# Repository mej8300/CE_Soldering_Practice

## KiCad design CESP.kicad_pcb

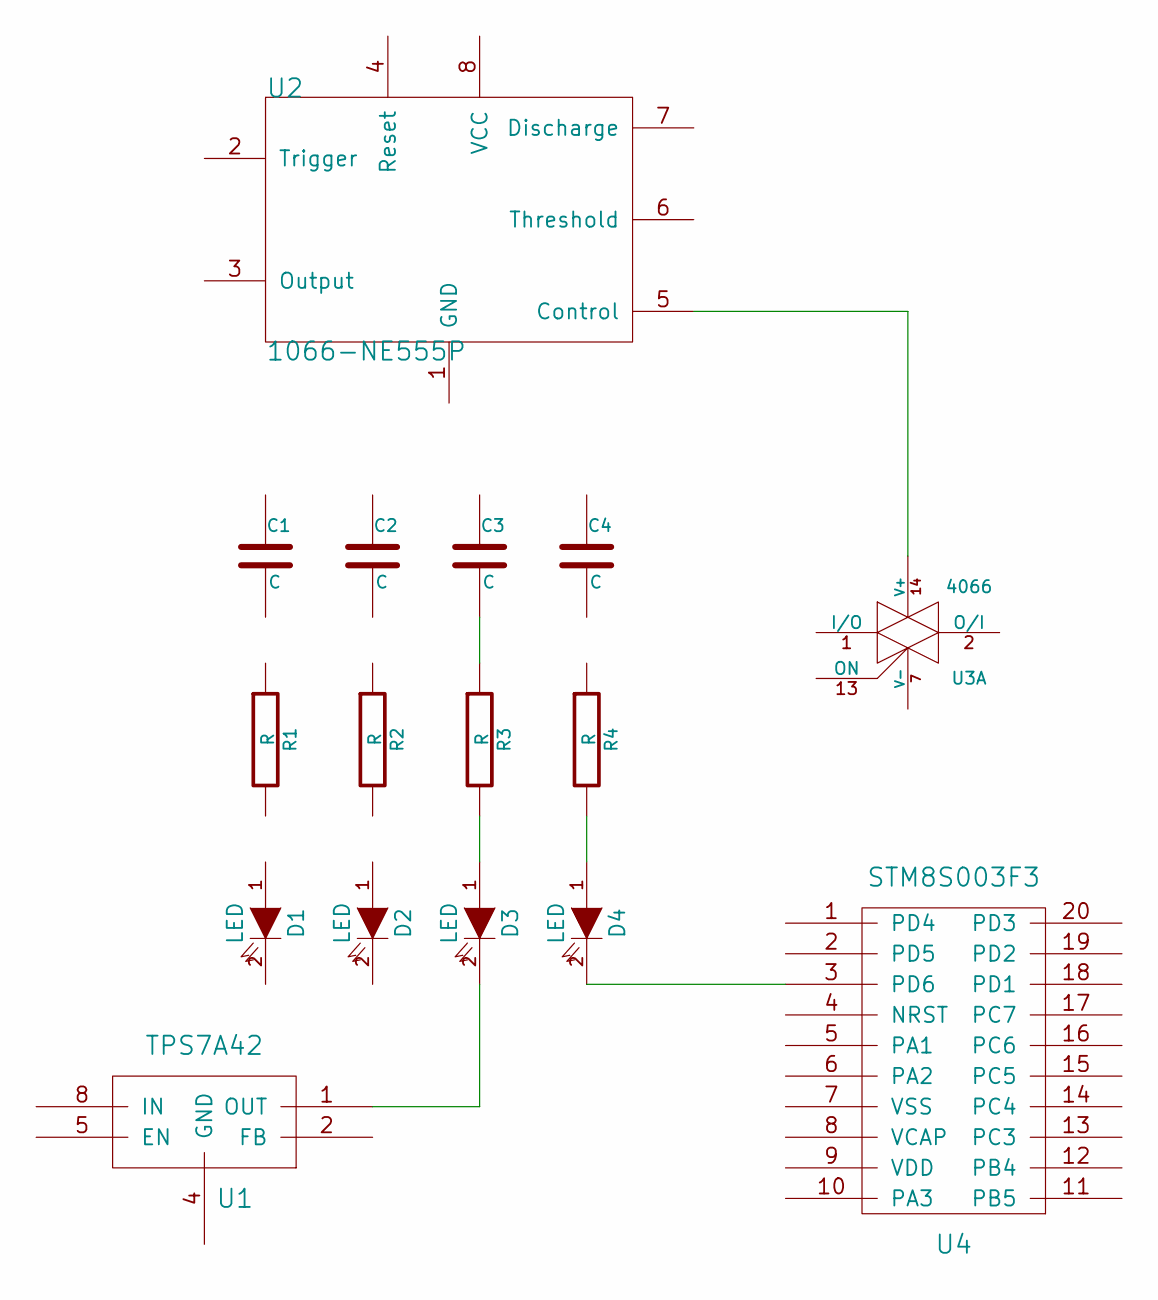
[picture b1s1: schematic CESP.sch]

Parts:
C1, C2, C3, C4: C
D1, D2, D3, D4: LED
R1, R2, R3, R4: R
U1: TPS7A42
U2: 1066-NE555P; andrew/b6d66
U3: 4066
U4: STM8S003F3

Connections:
unnamed: D4.1 (A), R4.2
unnamed: D3.1 (A), R3.2
unnamed: C3.2, R3.1
unnamed: D4.2 (K), U4.3 (PD6)
unnamed: U2.5 (Control), U3.14 (V+)
unnamed: D3.2 (K), U1.1 (OUT)

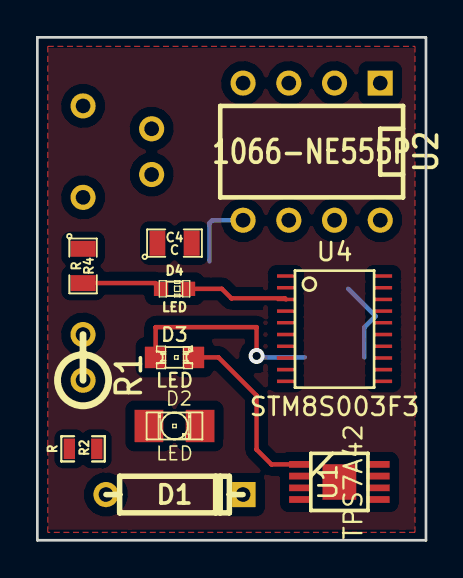
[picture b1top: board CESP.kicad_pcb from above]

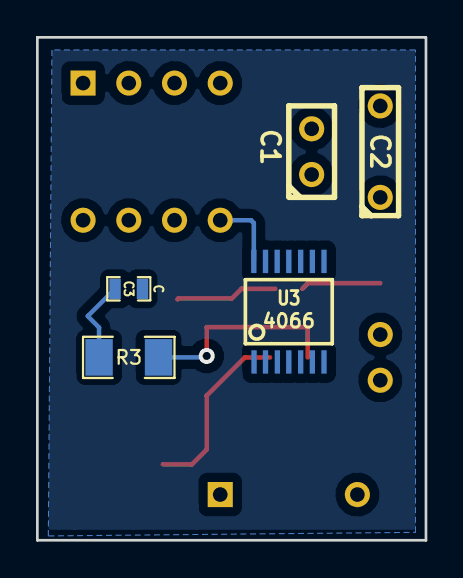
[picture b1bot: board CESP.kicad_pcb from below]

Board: 2 copper layers, 21.6 x 27.9 mm, 16 parts (5 on the bottom side), 6 nets.

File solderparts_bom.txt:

IC QUAD BILATERAL SWITCH 14-SOIC,	soic-14,	2.62,	http://www.digikey.dk/product-detail/en/CD4066BM96/296-14475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
IC REG LDO ADJ 50MA 8MSOP,			msop-8,		5.43,	http://www.digikey.dk/product-detail/en/TPS7A4201DGNR/296-30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
IC MCU 8BIT 8KB FLASH 20TSSOP,		tssop-20,	5.43,	http://www.digikey.dk/product-detail/en/STM8S003F3P6/497-119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
IC OSC MONO TIMING 8-DIP,			8-pdip,		1.97,	http://www.digikey.dk/product-detail/en/NA555P/296-21753-5-N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

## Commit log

2014-01-27 new solder board
2014-01-27 first draft
2014-01-27 drawing added
2014-02-03 new board
